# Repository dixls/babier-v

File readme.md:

# Babier-V

This is a 34 key unibody split keyboard called the Babier-V, inspired by the
Baby-V and the Vixen by eyeohdesigns, as well as ~30% boards like le Chiffre and
others.

### Layout

you can find the KLE json in [babier-v.json](babier-v.json).

Babier-V is currently very early in the design and protyping phase.

### Assembly

The current pcb design is a bare pcb for a pro-micro format controller and smd
diodes.

The printable case found in [print\ files/] uses a bumpon mounting style, where
bumpons are attached to the lobes of the plate and sit in the corresponding
divots in the case. The two halves of the case snap together, so no screws are
required. They may be difficult to print on smaller printers, but I managed to
get it done on a 225x225mm print bed.

### Project status

This project is effectively done. I may iterate and make a more polished version
in the future, but probably nothing big happening from this point.

### TODO:
- [X] Draft pro-micro based pcb
- [X] order pcb prototypes
- [X] draft zmk firmware
- [X] finish initial zmk firmware
    - it compiles fully, but is still untested
- [X] implement proper keymap in zmk
- [X] design plate
- [X] print plate
- [X] assemble prototype
- [X] test firmware
- [X] design printable case

### Future?:
- [ ] Design integrated pcb
- [ ] Design integrated wireless pcb?
- [ ] Design case for cnc

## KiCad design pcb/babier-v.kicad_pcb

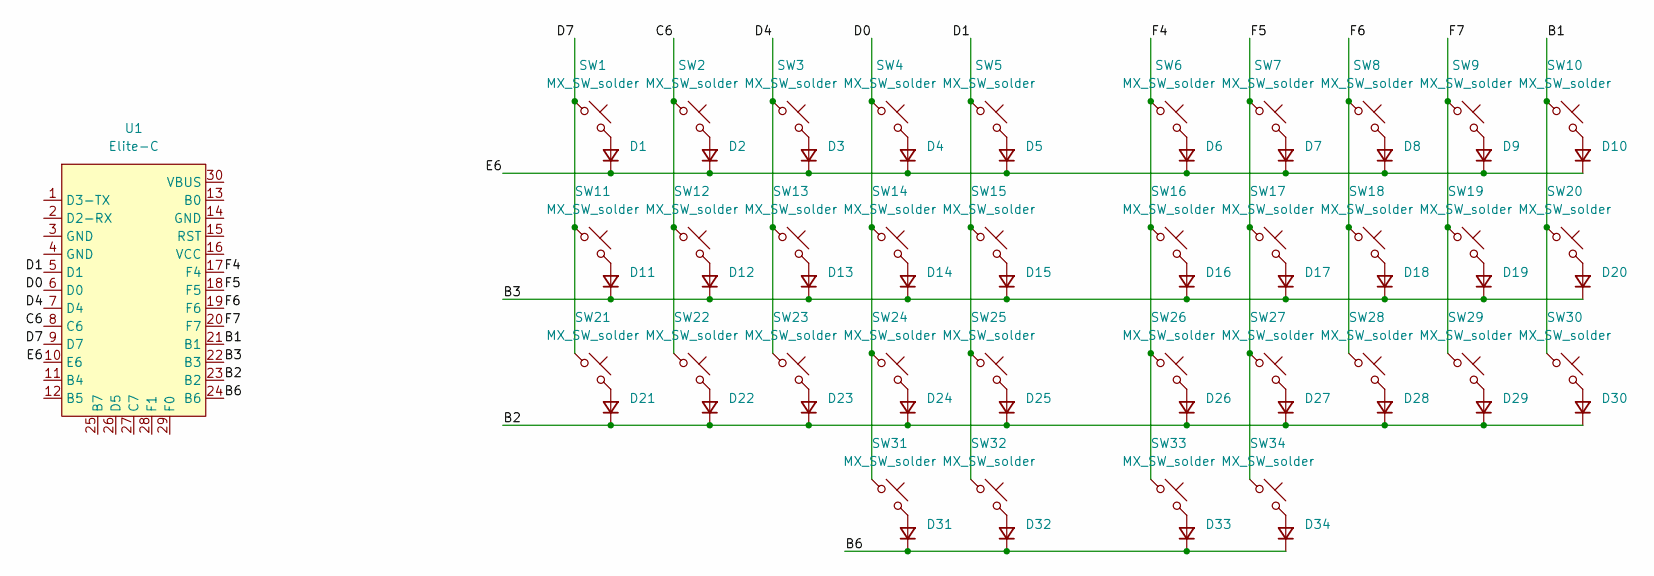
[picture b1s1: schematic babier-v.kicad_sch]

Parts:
D1, D2, D3, D4, D5, D6, D7, D8, D9, D10, D11, D12, D13, D14, D15, D16, D17, D18, D19, D20, D21, D22, D23, D24, D25, D26, D27, D28, D29, D30, D31, D32, D33, D34: D_Small; D_SOD-123
SW1, SW2, SW3, SW4, SW5, SW6, SW7, SW8, SW9, SW10, SW11, SW12, SW13, SW14, SW15, SW16, SW17, SW18, SW19, SW20, SW21, SW22, SW23, SW24, SW25, SW26, SW27, SW28, SW29, SW30, SW31, SW32, SW33, SW34: MX_SW_solder; SW_MX_1u
U1: Elite-C; Elite-C_ACH

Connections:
/B1: SW10.1, SW20.1, SW30.1, U1.21 (B1)
/B2: D21.1 (K), D22.1 (K), D23.1 (K), D24.1 (K), D25.1 (K), D26.1 (K), D27.1 (K), D28.1 (K), D29.1 (K), D30.1 (K), U1.23 (B2)
/B3: D11.1 (K), D12.1 (K), D13.1 (K), D14.1 (K), D15.1 (K), D16.1 (K), D17.1 (K), D18.1 (K), D19.1 (K), D20.1 (K), U1.22 (B3)
/B6: D31.1 (K), D32.1 (K), D33.1 (K), D34.1 (K), U1.24 (B6)
/C6: SW2.1, SW12.1, SW22.1, U1.8 (C6)
/D0: SW4.1, SW14.1, SW24.1, SW31.1, U1.6 (D0)
/D1: SW5.1, SW15.1, SW25.1, SW32.1, U1.5 (D1)
/D4: SW3.1, SW13.1, SW23.1, U1.7 (D4)
/D7: SW1.1, SW11.1, SW21.1, U1.9 (D7)
/E6: D1.1 (K), D2.1 (K), D3.1 (K), D4.1 (K), D5.1 (K), D6.1 (K), D7.1 (K), D8.1 (K), D9.1 (K), D10.1 (K), U1.10 (E6)
/F4: SW6.1, SW16.1, SW26.1, SW33.1, U1.17 (F4)
/F5: SW7.1, SW17.1, SW27.1, SW34.1, U1.18 (F5)
/F6: SW8.1, SW18.1, SW28.1, U1.19 (F6)
/F7: SW9.1, SW19.1, SW29.1, U1.20 (F7)
unnamed: D1.2 (A), SW1.2
unnamed: D2.2 (A), SW2.2
unnamed: D3.2 (A), SW3.2
unnamed: D4.2 (A), SW4.2
unnamed: D5.2 (A), SW5.2
unnamed: D6.2 (A), SW6.2
unnamed: D7.2 (A), SW7.2
unnamed: D8.2 (A), SW8.2
unnamed: D9.2 (A), SW9.2
unnamed: D10.2 (A), SW10.2
unnamed: D11.2 (A), SW11.2
unnamed: D12.2 (A), SW12.2
unnamed: D13.2 (A), SW13.2
unnamed: D14.2 (A), SW14.2
unnamed: D15.2 (A), SW15.2
unnamed: D16.2 (A), SW16.2
unnamed: D17.2 (A), SW17.2
unnamed: D18.2 (A), SW18.2
unnamed: D19.2 (A), SW19.2
unnamed: D20.2 (A), SW20.2
unnamed: D21.2 (A), SW21.2
unnamed: D22.2 (A), SW22.2
unnamed: D23.2 (A), SW23.2
unnamed: D24.2 (A), SW24.2
unnamed: D25.2 (A), SW25.2
unnamed: D26.2 (A), SW26.2
unnamed: D27.2 (A), SW27.2
unnamed: D28.2 (A), SW28.2
unnamed: D29.2 (A), SW29.2
unnamed: D30.2 (A), SW30.2
unnamed: D31.2 (A), SW31.2
unnamed: D32.2 (A), SW32.2
unnamed: D33.2 (A), SW33.2
unnamed: D34.2 (A), SW34.2

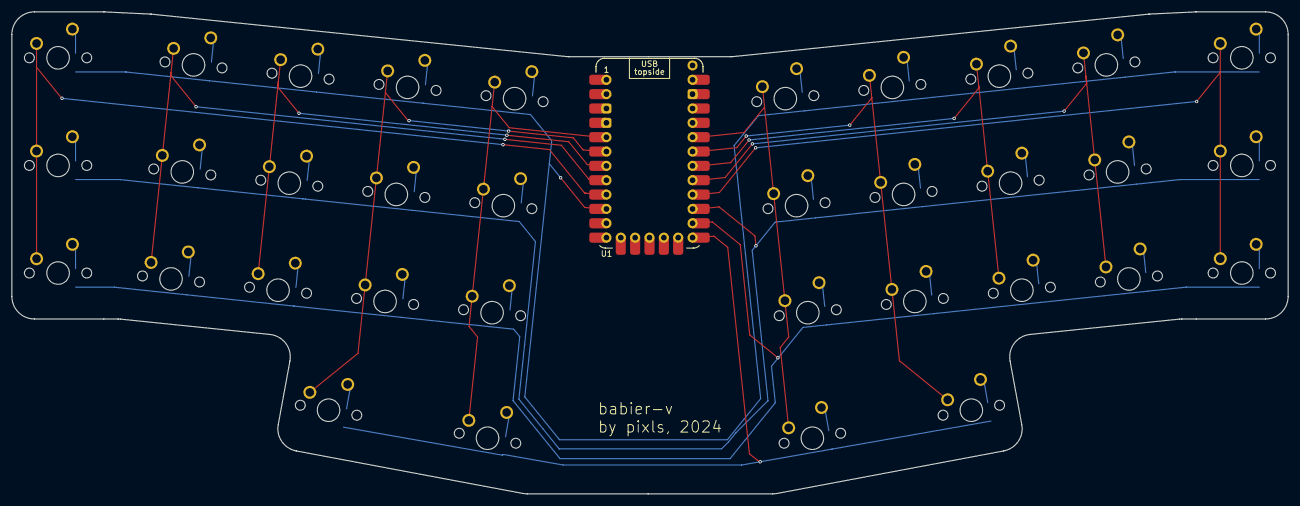
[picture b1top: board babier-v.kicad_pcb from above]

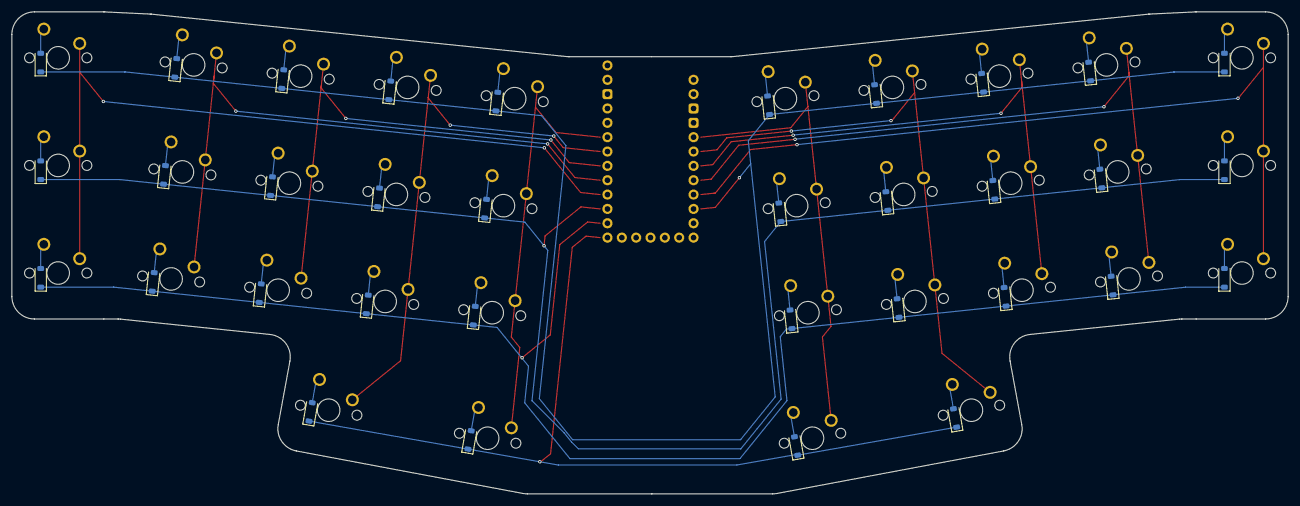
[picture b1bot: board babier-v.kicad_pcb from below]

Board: 2 copper layers, 225.9 x 85.3 mm, 69 parts (34 on the bottom side), 48 nets.

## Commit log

2024-12-13 Restart with KLE based kicad project
    The inital repo was for an ergogen based project, but instead of
    relearning ergogen, I decided to uh, learn kicad, i guess.
2024-12-13 add zmk config as submodule of the main project
2024-12-13 add readme
2024-12-13 readme: formatting
2024-12-13 add images to readme
2024-12-13 add gitignore
2024-12-14 small pcb changes, update todos
2025-01-02 bring in updated firmware, update readme, add print files
2025-01-24 Add plate step & astra case, reorganize case files
    Add step and fusion file for bump-on mount thick plate. Add step files
    for Astra's new case. Reorganize case files.
    TODO: Add a readme for each case?
2025-02-03 add additional case files
